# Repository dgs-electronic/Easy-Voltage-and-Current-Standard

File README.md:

# Easy-Voltage-and-Current-Standard

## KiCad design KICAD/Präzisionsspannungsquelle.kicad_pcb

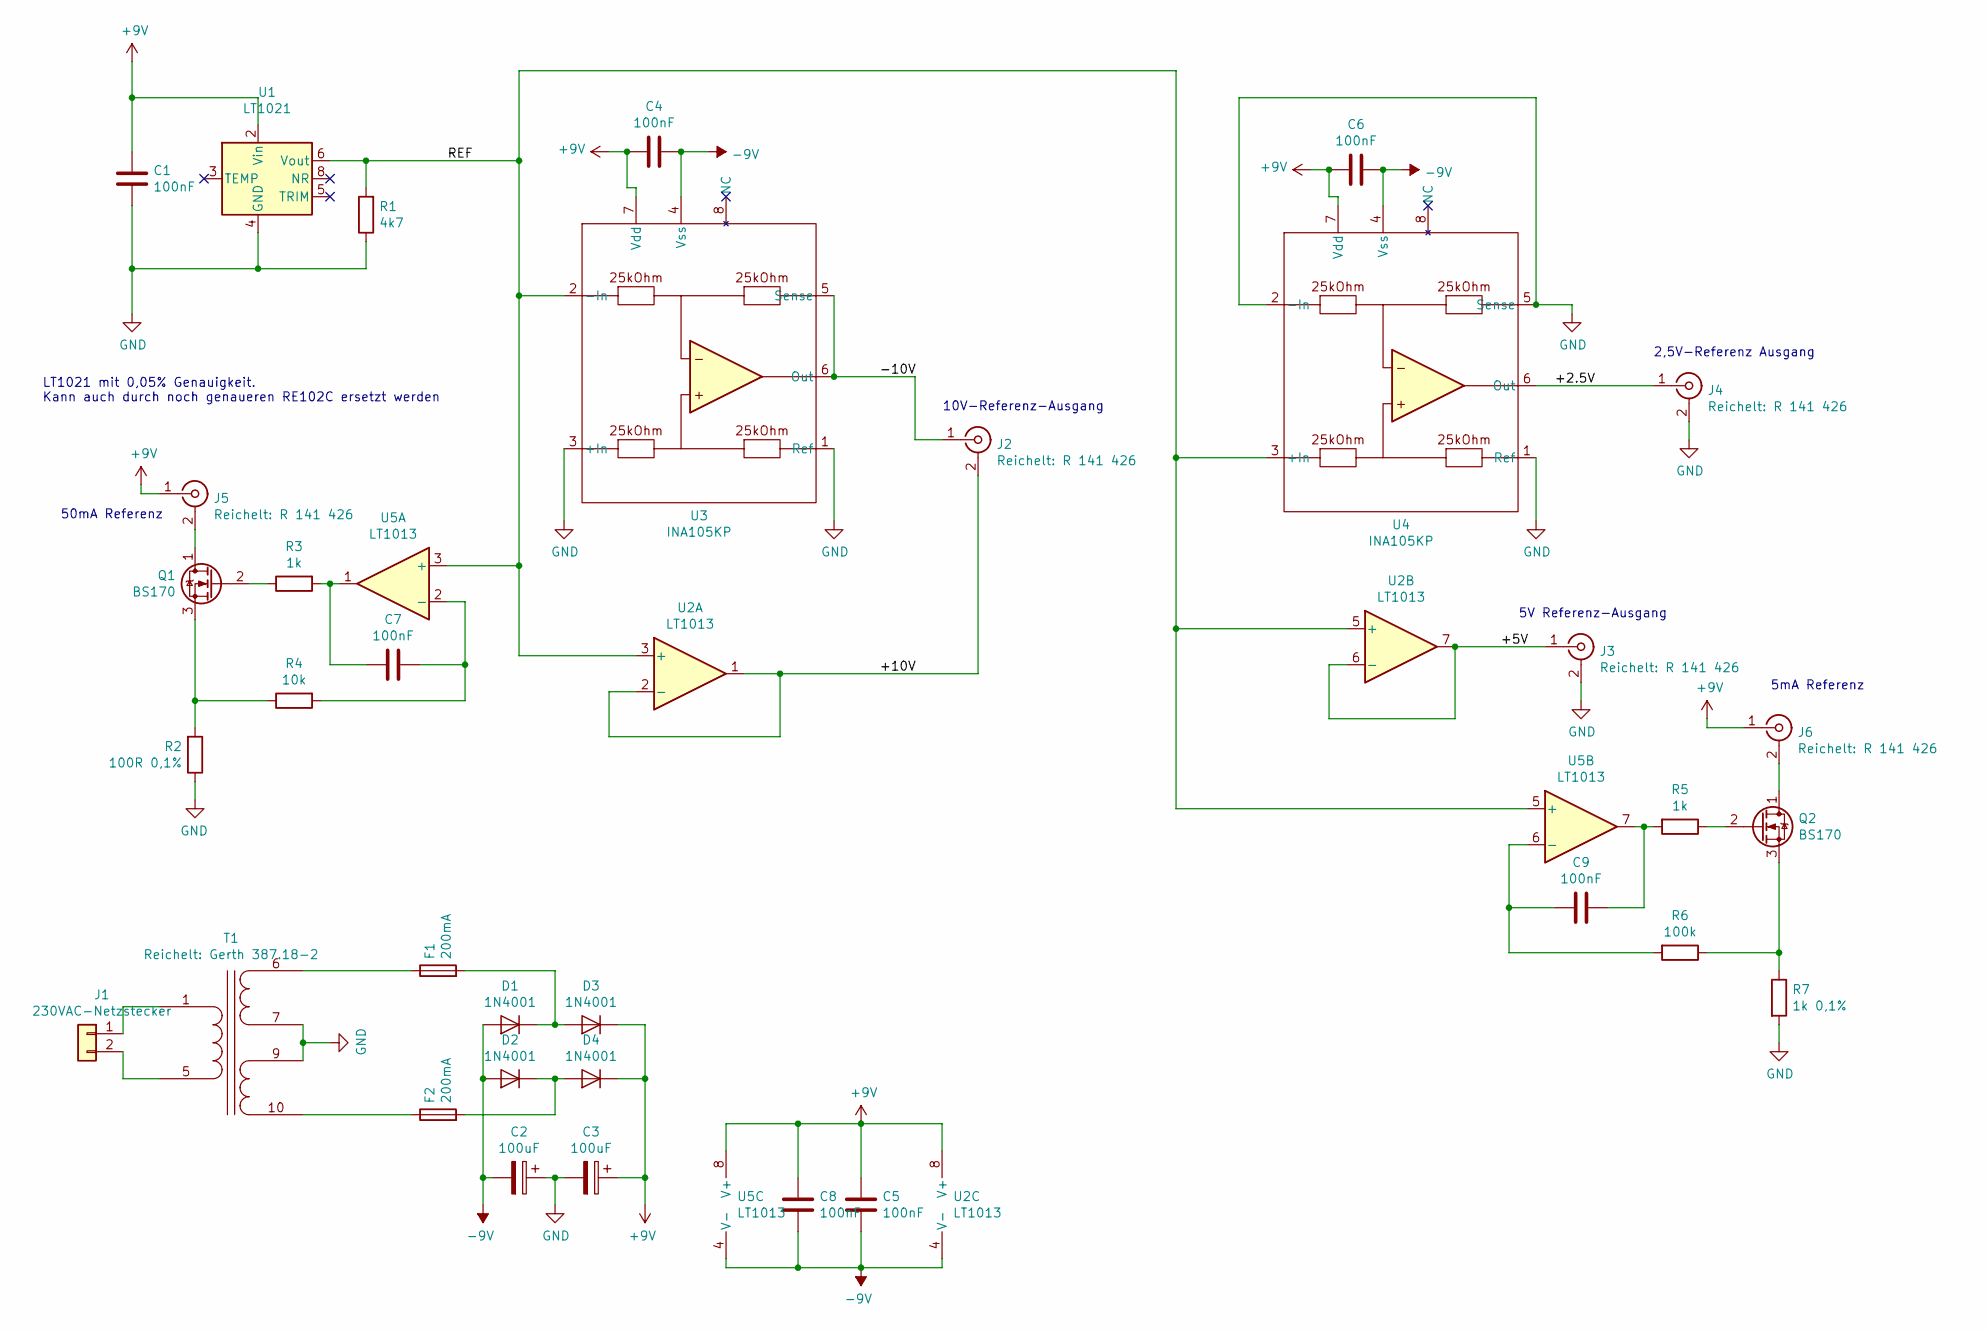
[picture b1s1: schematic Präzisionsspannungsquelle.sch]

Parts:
C1, C4, C5, C6, C7, C8, C9: 100nF; C_Disc_D3.8mm_W2.6mm_P2.50mm
C2, C3: 100uF; CP_Radial_D10.0mm_P5.00mm
D1, D2, D3, D4: 1N4001; D_DO-41_SOD81_P10.16mm_Horizontal
F1, F2: 200mA; Fuseholder5x20_horiz_SemiClosed_Casing10x25mm
J1: 230VAC-Netzstecker; PhoenixContact_GMSTB-GF_02x7.62mm_Angled_ThreadedFlange
J2, J3, J4, J5, J6: Reichelt: R 141 426; Print-BNC-REICHELT
Q1, Q2: BS170; TO-92_Inline_Wide
R1: 4k7; R_Axial_DIN0414_L11.9mm_D4.5mm_P15.24mm_Horizontal
R2: 100R 0,1%; R_Axial_DIN0414_L11.9mm_D4.5mm_P15.24mm_Horizontal
R3, R5: 1k; R_Axial_DIN0414_L11.9mm_D4.5mm_P15.24mm_Horizontal
R4: 10k; R_Axial_DIN0414_L11.9mm_D4.5mm_P15.24mm_Horizontal
R6: 100k; R_Axial_DIN0414_L11.9mm_D4.5mm_P15.24mm_Horizontal
R7: 1k 0,1%; R_Axial_DIN0414_L11.9mm_D4.5mm_P15.24mm_Horizontal
T1: Reichelt: Gerth 387.18-2; Transformer_Gerth_387.18.2-40,6x34,2
U1: LT1021; DIP-8_W7.62mm_LongPads
U2, U5: LT1013; DIP-8_W7.62mm_LongPads
U3, U4: INA105KP; DIP-8_W7.62mm_LongPads

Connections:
+9V: C1.1, C3.1, C4.2, C5.1, C6.2, C8.1, D3.1 (K), D4.1 (K), J5.1 (In), J6.1 (In), U1.2 (Vin), U2.8 (V+), U3.7 (Vdd), U4.7 (Vdd), U5.8 (V+)
-9V: C2.2, C4.1, C5.2, C6.1, C8.2, D1.2 (A), D2.2 (A), U2.4 (V-), U3.4 (Vss), U4.4 (Vss), U5.4 (V-)
/+2.5V: J4.1 (In), U4.6 (Out)
/+5V: J3.1 (In), U2.6 (-), U2.7
/+10V: J2.2 (Ext), U2.1, U2.2 (-)
/-10V: J2.1 (In), U3.5 (Sense), U3.6 (Out)
/REF: R1.2, U1.6 (Vout), U2.3 (+), U2.5 (+), U3.2 (-In), U4.3 (+In), U5.3 (+), U5.5 (+)
GND: C1.2, C2.1, C3.2, J3.2 (Ext), J4.2 (Ext), R1.1, R2.1, R7.2, T1.7 (SB), T1.9 (SC), U1.4 (GND), U3.1 (Ref), U3.3 (+In), U4.1 (Ref), U4.2 (-In), U4.5 (Sense)
unnamed: C7.1, R3.2, U5.1
unnamed: C7.2, R4.2, U5.2 (-)
unnamed: C9.1, R5.2, U5.7
unnamed: C9.2, R6.2, U5.6 (-)
unnamed: D1.1 (K), D3.2 (A), F1.2
unnamed: D2.1 (K), D4.2 (A), F2.2
unnamed: F1.1, T1.6 (SA)
unnamed: F2.1, T1.10 (SD)
unnamed: J1.1, T1.1 (AA)
unnamed: J1.2, T1.5 (AB)
unnamed: J5.2 (Ext), Q1.1 (D)
unnamed: J6.2 (Ext), Q2.1 (D)
unnamed: Q1.2 (G), R3.1
unnamed: Q1.3 (S), R2.2, R4.1
unnamed: Q2.2 (G), R5.1
unnamed: Q2.3 (S), R6.1, R7.1

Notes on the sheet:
10V-Referenz-Ausgang
2,5V-Referenz Ausgang
5V Referenz-Ausgang
LT1021 mit 0,05% Genauigkeit. Kann auch durch noch genaueren RE102C ersetzt werden
50mA Referenz
5mA Referenz

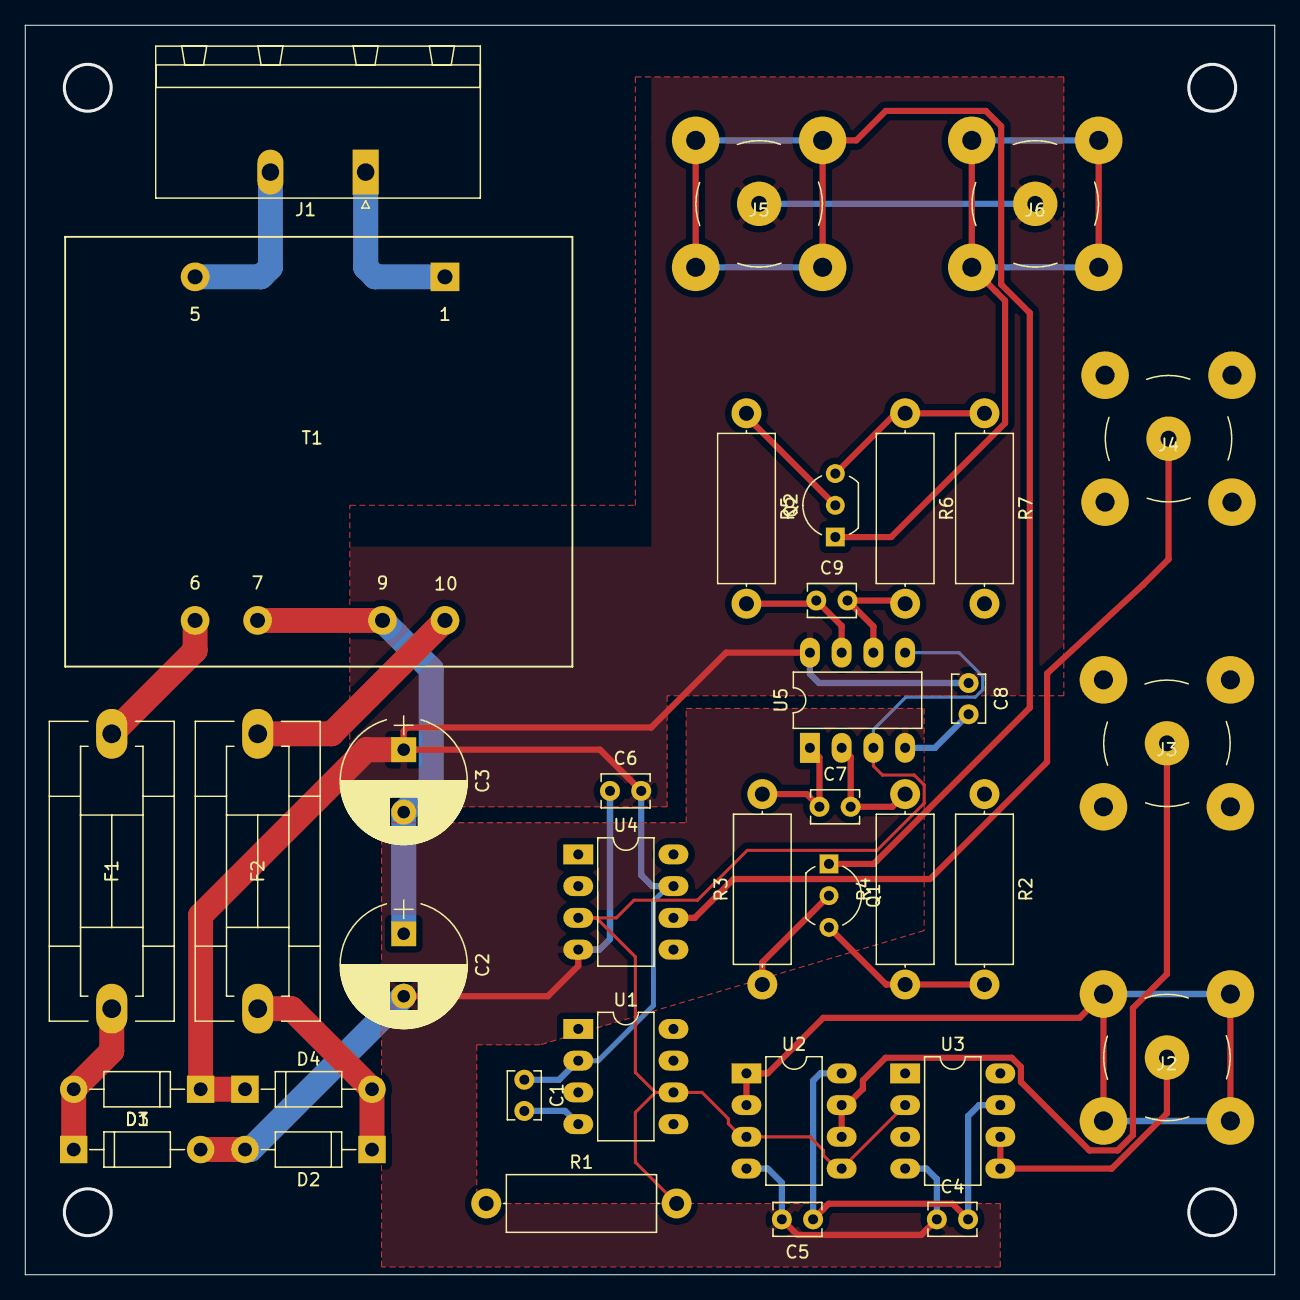
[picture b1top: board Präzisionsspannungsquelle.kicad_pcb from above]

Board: 2 copper layers, 100.0 x 100.0 mm, 36 parts (0 on the bottom side), 24 nets.

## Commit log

2019-12-01 KICAD Project
